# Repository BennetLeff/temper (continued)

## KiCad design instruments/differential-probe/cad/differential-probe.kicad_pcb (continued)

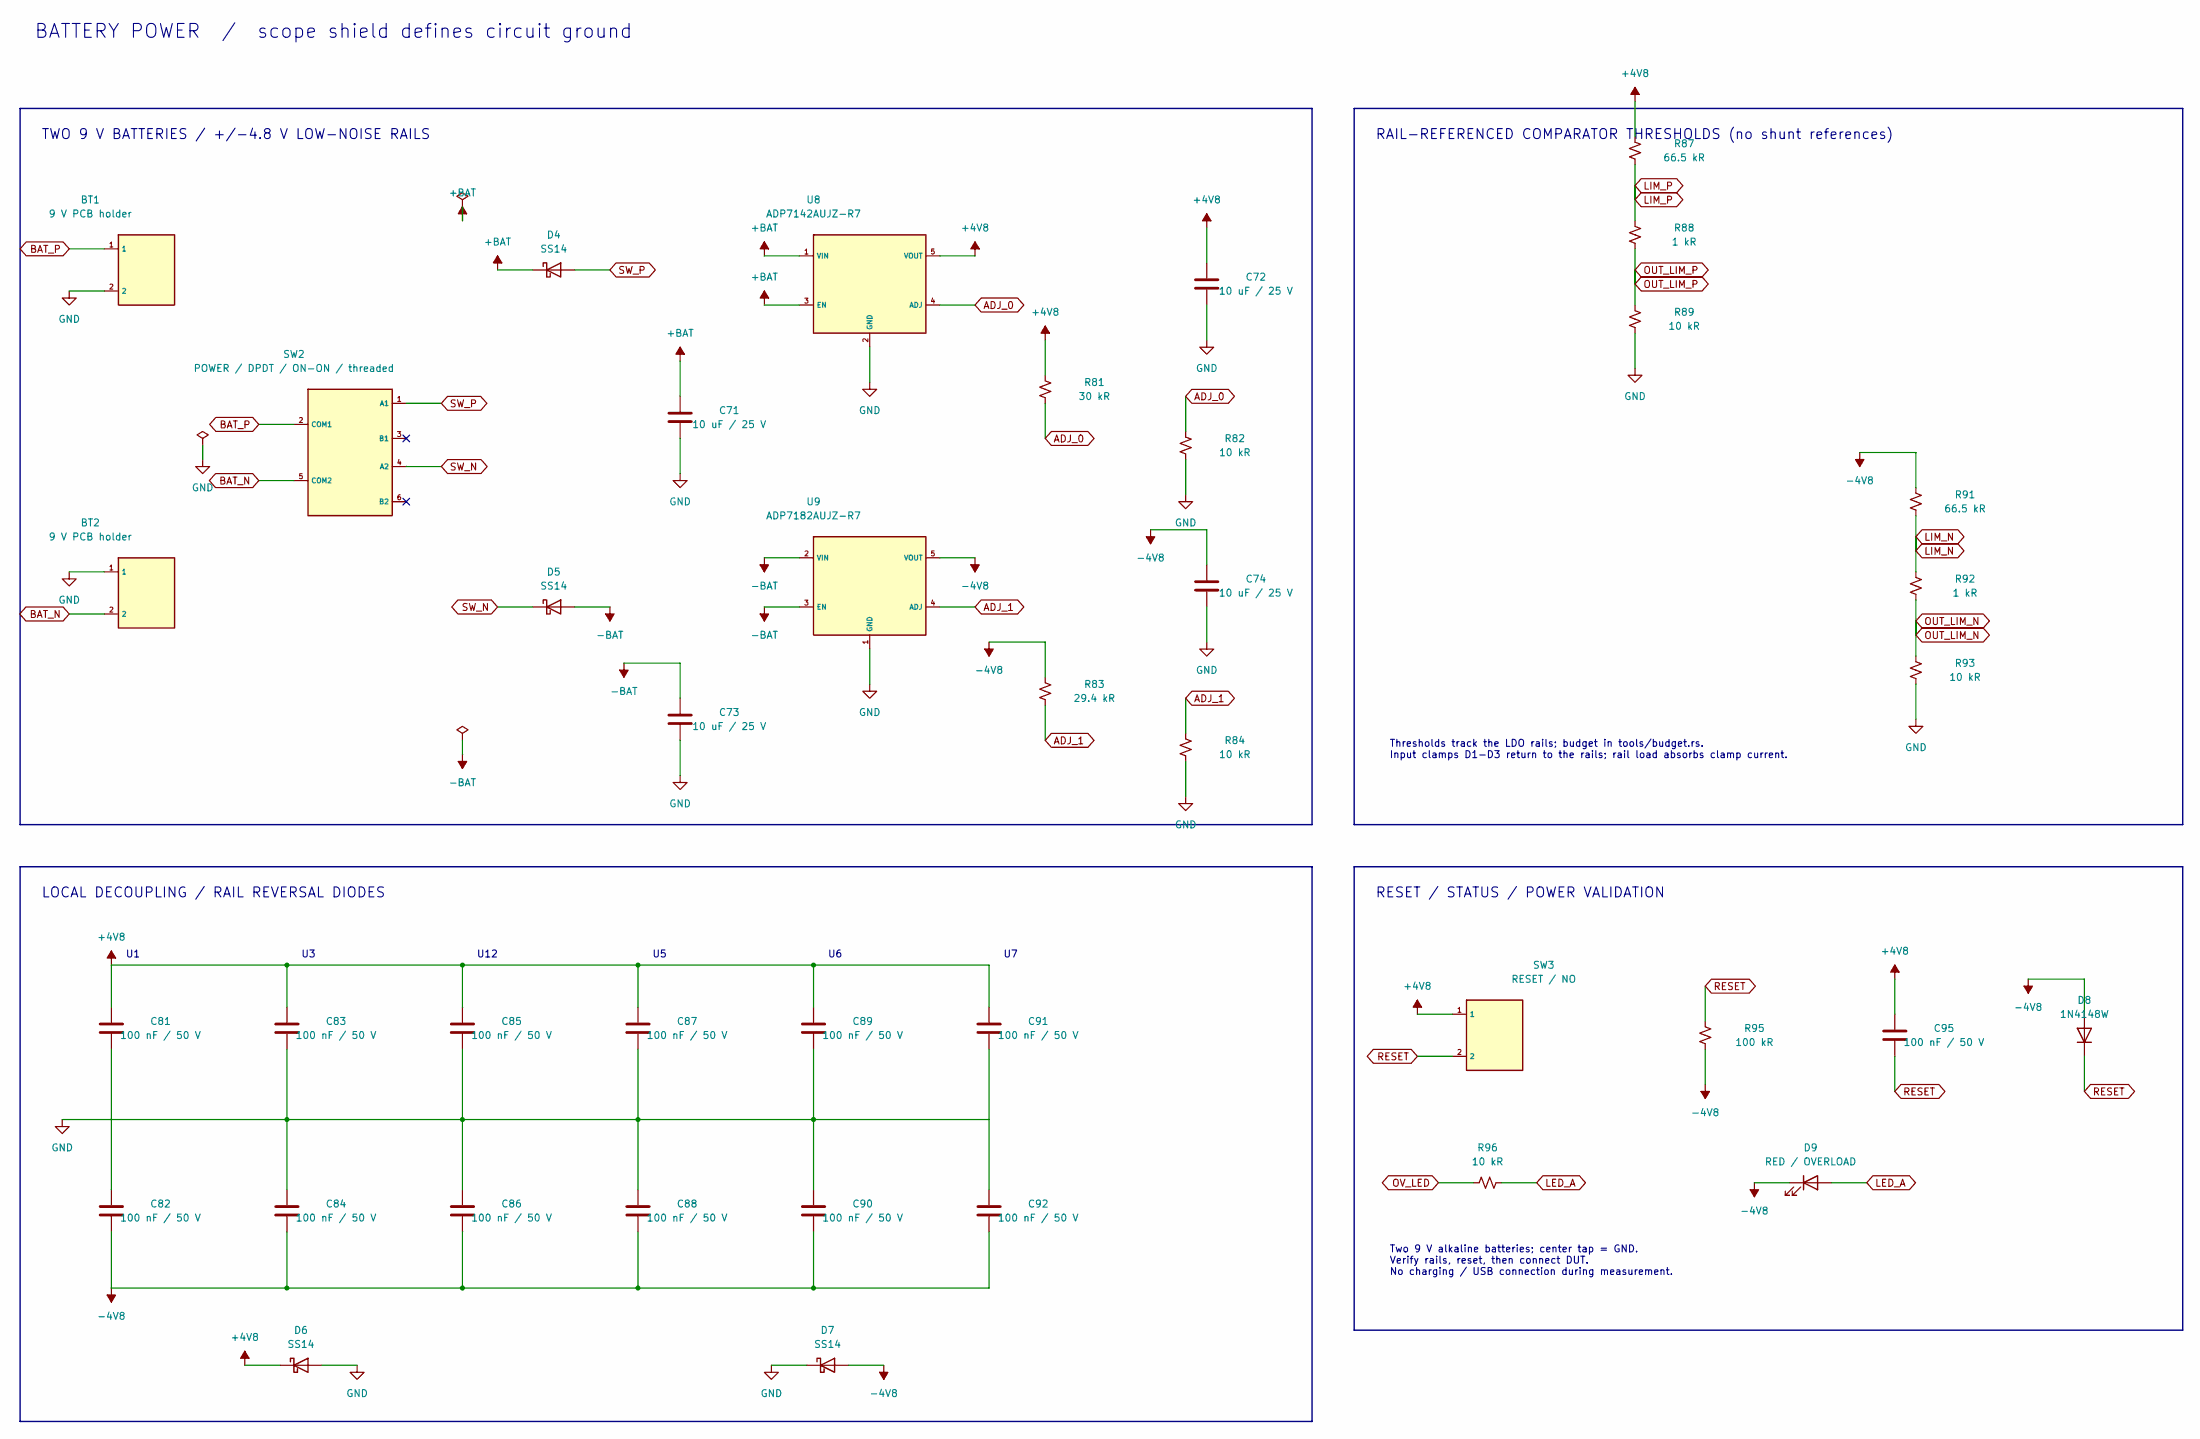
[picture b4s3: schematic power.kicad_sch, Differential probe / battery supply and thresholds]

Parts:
BT1, BT2: 9 V PCB holder; BatteryHolder_MPD_BH9VPC; MPN BH9VPC
C71, C72, C73, C74: 10 uF / 25 V; C_1210_3225Metric; MPN C3225X7R1E106KTJ00N; LCSC C342744
C81, C82, C83, C84, C85, C86, C87, C88, C89, C90, C91, C92, C95: 100 nF / 50 V; C_0805_2012Metric; MPN CC0805KRX7R9BB104; LCSC C49678
D4, D5, D6, D7: SS14; D_SMA; MPN SS14; LCSC C2480
D8: 1N4148W; D_SOD-123; MPN 1N4148W; LCSC C81598
D9: RED / OVERLOAD; LED_0805_2012Metric; MPN NCD0805R1; LCSC C84256
R81: 30 kR; R_0805_2012Metric; MPN RT0805BRD0730KL
R82, R84, R89, R93, R96: 10 kR; R_0805_2012Metric; MPN RT0805BRD0710KL
R83: 29.4 kR; R_0805_2012Metric; MPN RT0805BRD0729K4L
R87, R91: 66.5 kR; R_0805_2012Metric; MPN RT0805BRD0766K5L
R88, R92: 1 kR; R_0805_2012Metric; MPN 0805W8F1001T5E; LCSC C17513
R95: 100 kR; R_0805_2012Metric; MPN 0805W8F1003T5E; LCSC C149504
SW2: POWER / DPDT / ON-ON / threaded; ESwitch_100_M7_DPDT; MPN 100DP1T1B1M7QEH
SW3: RESET / NO; SW_Tactile_CK_PTS645_THT; MPN PTS645SL43-2 LFS; LCSC C221874
U8: ADP7142AUJZ-R7; TSOT-23-5; MPN ADP7142AUJZ-R7; LCSC C514356
U9: ADP7182AUJZ-R7; TSOT-23-5; MPN ADP7182AUJZ-R7; LCSC C514358

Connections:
+4V8: C72.1, C81.1, C83.1, C85.1, C87.1, C89.1, C91.1, C95.1, D6.1 (K), R81.1, R87.1, SW3.1, U8.5 (VOUT); also elsewhere on the board
+BAT: C71.1, D4.1 (K), U8.1 (VIN), U8.3 (EN)
-4V8: C74.1, C82.2, C84.2, C86.2, C88.2, C90.2, C92.2, D7.2 (A), D8.2 (A), D9.1 (K), R83.1, R91.1, R95.2, U9.5 (VOUT); also elsewhere on the board
-BAT: C73.1, D5.2 (A), U9.2 (VIN), U9.3 (EN)
ADJ_0: R81.2, R82.1, U8.4 (ADJ)
ADJ_1: R83.2, R84.1, U9.4 (ADJ)
BAT_N: BT2.2, SW2.5 (COM2)
BAT_P: BT1.1, SW2.2 (COM1)
GND: BT1.2, BT2.1, C71.2, C72.2, C73.2, C74.2, C81.2, C82.1, C83.2, C84.1, C85.2, C86.1, C87.2, C88.1, C89.2, C90.1, C91.2, C92.1, D6.2 (A), D7.1 (K), R82.2, R84.2, R89.2, R93.2, U8.2 (GND), U9.1 (GND); also elsewhere on the board
LED_A: D9.2 (A), R96.2
LIM_N: R91.2, R92.1; also elsewhere on the board
LIM_P: R87.2, R88.1; also elsewhere on the board
OUT_LIM_N: R92.2, R93.1; also elsewhere on the board
OUT_LIM_P: R88.2, R89.1; also elsewhere on the board
OV_LED: R96.1; also elsewhere on the board
RESET: C95.2, D8.1 (K), R95.1, SW3.2; also elsewhere on the board
SW_N: D5.1 (K), SW2.4 (A2)
SW_P: D4.2 (A), SW2.1 (A1)

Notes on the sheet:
BATTERY POWER / scope shield defines circuit ground
TWO 9 V BATTERIES / +/-4.8 V LOW-NOISE RAILS
RAIL-REFERENCED COMPARATOR THRESHOLDS (no shunt references)
Thresholds track the LDO rails; budget in tools/budget.rs. Input clamps D1-D3 return to the rails; rail load absorbs clamp current.
LOCAL DECOUPLING / RAIL REVERSAL DIODES
U12
RESET / STATUS / POWER VALIDATION
Two 9 V alkaline batteries; center tap = GND. Verify rails, reset, then connect DUT. No charging / USB connection during measurement.

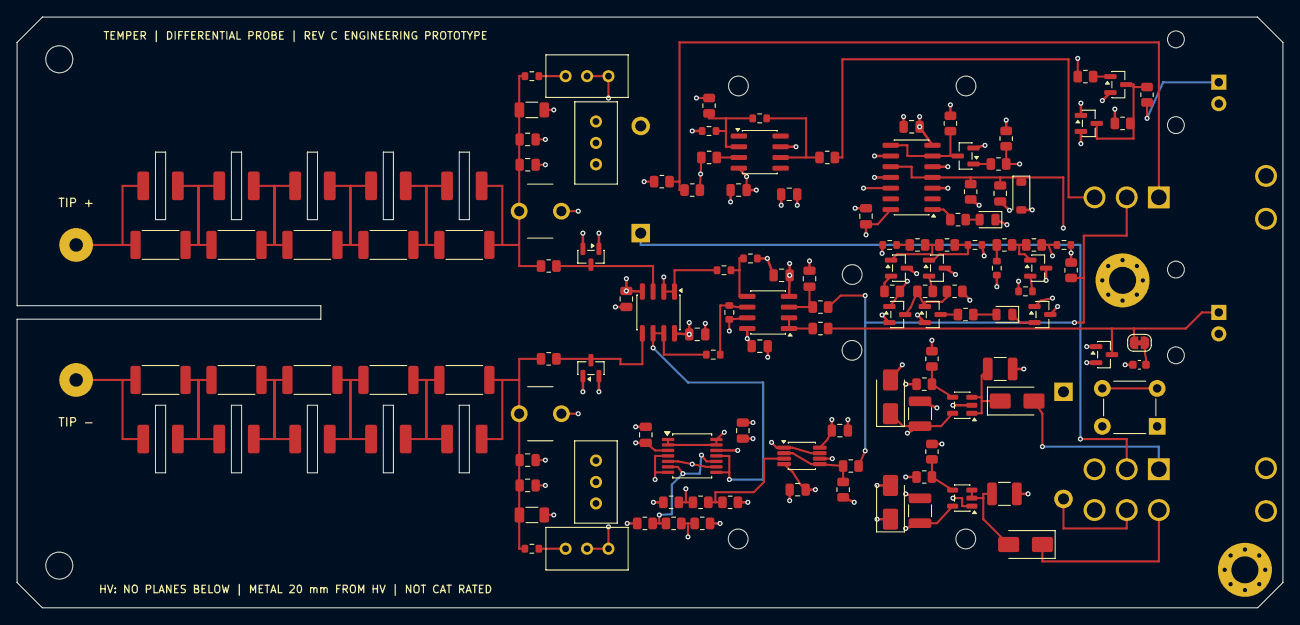
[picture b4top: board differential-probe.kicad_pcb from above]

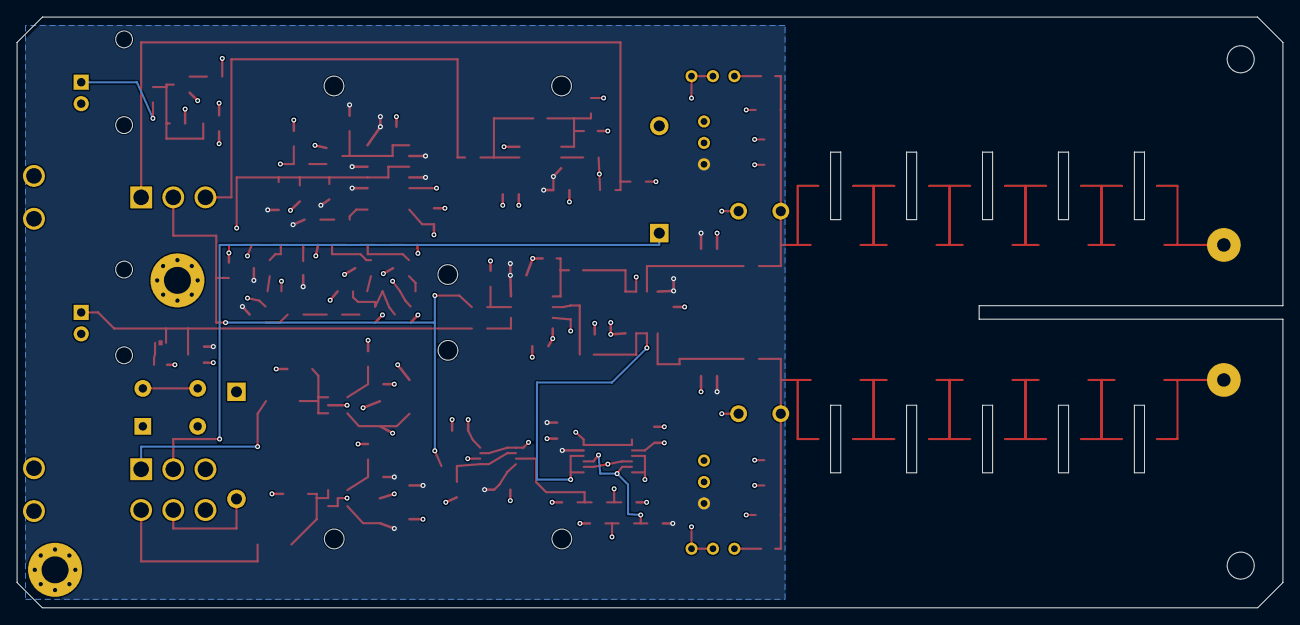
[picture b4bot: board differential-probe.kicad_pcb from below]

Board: 4 copper layers, 150.0 x 70.0 mm, 143 parts (2 on the bottom side), 73 nets.

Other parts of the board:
H1: H1; MountingHole_3.2mm_M3_Pad_Via
H2: H2; MountingHole_3.2mm_M3_Pad_Via
H3: H3; MountingHole_3.2mm_M3
H4: H4; MountingHole_3.2mm_M3
W_HV1: W_HV1; HV_Captive_Lead
W_HV2: W_HV2; HV_Captive_Lead

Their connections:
GND: H1.1, H2.1; also elsewhere on the board
TIP_N: W_HV2.1; also elsewhere on the board
TIP_P: W_HV1.1; also elsewhere on the board

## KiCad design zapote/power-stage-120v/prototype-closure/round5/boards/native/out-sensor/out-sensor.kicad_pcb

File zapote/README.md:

# Zapote

**Board checks:** [ERC, DRC and layout command index](CHECKS.md), or
`make -C zapote help`. Includes native current analysis, before/after comparisons,
Rust owners, test evidence, and the current integration/CI checkpoint.

> **Scope on `main` (landed 2026-10-08).** Five maintained units — RTD, current-sense,
> thermal-sense, interlock, gate-drive — plus `power-stage-120v` and the inverter
> measurement framework (superseded by the 120 V stage's own validation plan; see
> `inverter/U3-MEASUREMENT-READINESS.md`). The Rev38 PFC power entry, the voltage-sense unit, the
> PFC-board bridge/shunt FEM and cooling studies, and their crate modules are
> archived at tags `archive/rev38-power-entry-2026-09-25` and
> `archive/zapote-coil-intake-2026-09-25` (see `docs/archive/REV38.md`). Unit
> evidence runs not read by a check also stay in those tags; a unit
> `ACCEPTANCE.md` path that is absent here resolves there. Bulk solver output
> (`*.gz`, `*.npz`, files over 5 MB) is in release `zapote-evidence-2026-10-08`;
> `python3 zapote/tools/evidence_archive.py fetch` restores it in place.

Zapote is Temper's agent engineering subproject centered on a large Rust
validation suite. The working Python/KiCad editing adapter stays in use.

It shares Temper's product inputs and copies needed existing Rust validators
into focused packages such as `zapote-drc` and `zapote-erc`, retaining tests and
provenance. The agent makes placement and routing decisions; Zapote supplies
explicit board edits, engineering feedback, memory, and recorded execution.
See [ARCHITECTURE.md](ARCHITECTURE.md) for package boundaries and
[VALIDATION.md](VALIDATION.md) for the board-validation objective and coverage
ambition. Replacing the Python adapter is deferred.

The [cooker delivery roadmap](https://github.com/BennetLeff/temper/blob/archive/zapote-coil-intake-2026-09-25/docs/plans/2026-09-10-1627-zapote-cooker-roadmap-plan.md)
sets the order from standalone buck/MCU units through the complete routed board and
physical bring-up. Each milestone adds cooker circuitry, Rust validation coverage
and reusable engineering lessons; implementation detail is added as it approaches.

## Current status

Zapote has a standalone Rust workspace with core, DRC, ERC and harness packages.
The [RTD unit](rtd/unit/ACCEPTANCE.md) exercises the source-to-board flow, and
[model qualification](rtd/model-correctness/README.md) checks the meaning of its
passive-network certificates. Device applicability and brownout timing remain
INDETERMINATE; physical tests are NOT RUN.

The [standalone current-sense / primary OCP unit](current-sense/README.md)
adds a separately compiled Atopile source, routed native PCB, corrected
transformer land pattern, bounded electrical model and Rust source/geometry
checks. Its acceptance record separates digital verification from unrun
physical qualification and procurement gaps.

The [standalone voltage-sense / OVP unit](https://github.com/BennetLeff/temper/blob/archive/zapote-coil-intake-2026-09-25/zapote/voltage-sense/README.md) adds the next separately compiled, routed unit, a corrected ADC divider, source-derived electrical checks and saved-document consistency controls. Its digital construction passes while qualification remains explicit.

The [standalone thermal unit](thermal-sense/README.md) adds two external-NTC channels, loaded-feedback trip/release modeling, exact connectivity controls and a routed native PCB. Rev B adds conditional open-wire detection; physical qualification remains separate.

The [isolated gate-drive unit](gate-drive/README.md) has a routed 100 × 80 mm candidate with clean native ERC/DRC and passing Rust construction checks; physical qualification is unrun. The [active PFC power-entry unit](https://github.com/BennetLeff/temper/blob/archive/zapote-coil-intake-2026-09-25/zapote/power-entry/README.md) preserves the 1,800 W nominal AC-input target. Its 54-component, 230 × 210 mm candidate is routed with zero native ERC/DRC findings or unconnected nets and seven passing Rust construction findings. Qualification remains INDETERMINATE. See the [two-board demo](https://github.com/BennetLeff/temper/blob/archive/zapote-coil-intake-2026-09-25/zapote/demo-gate-power/index.html).

The [Rust coverage inventory](validation/inventory-2026-09-12.json) maps Temper donors to Zapote,
lists the checks recorded for each maintained unit, and orders the next ports.
The `zapote-board` CLI checks physical stackup only. The [check index](CHECKS.md)
lists the separate native layout/current and unit electrical-validation commands.

[Engineering memory](https://github.com/BennetLeff/temper/blob/archive/zapote-coil-intake-2026-09-25/zapote/skills/README.md) connects reviewed, versioned lessons to
construction inputs through Rust selection and a thin process transport (the catalog and
Python transport are archived; the Rust policy remains in `zapote-harness`). The
native KiCad adapters live in `harness-lab/`, the generators in `tools/generators/`
and the atopile base library in `elec-base/src`. The old Python
migration outline is superseded by [MIGRATION.md](https://github.com/BennetLeff/temper/blob/archive/zapote-coil-intake-2026-09-25/zapote/MIGRATION.md).

The [Gmsh + Elmer thermal backend](https://github.com/BennetLeff/temper/blob/archive/zapote-coil-intake-2026-09-25/zapote/thermal/README.md) adds a separate external
electrothermal reference path, orchestrated and checked in Rust. Its copper-bar
benchmark establishes solver setup; it does not qualify the power-entry necks
or replace existing board findings.

## Layout

| Path | Purpose |
|---|---|
| `project.toml` | Zapote identity and shared Temper resource map |
| `AGENTS.md` | Local operating rules for work in this project |
| `Makefile` | Rust build/test and common saved-board gates |
| `CHECKS.md` | Check discovery: commands, scope, code owners, evidence and CI status |
| `layout-quality/` | Native geometry/current feedback and supplied-model check catalog |
| `Cargo.toml`, `packages/` | Rust workspace, validators and harness |
| `ports.toml` | Donor hashes, copied tests and extraction changes |
| `validation/` | Dated donor inventory, per-unit coverage and next-port sequence |
| `thermal/` | Gmsh + Elmer backend scope, native installation and reference evidence |
| `ARCHITECTURE.md` | Rust package ownership and agent/validator contract |
| `experiments/` | Experiment definitions and frozen inputs |
| `skills/` | Versioned agent skills and learned artifacts |
| `artifacts/` | Durable evidence manifests and local artifact indexes |
| `runs/` | Git-ignored runtime output |
| `evidence-archive.json` | Manifest of bulk evidence held in release assets; restore with `tools/evidence_archive.py fetch` |
| `docs/` | Design, migration, and operating notes |

## Commands

```sh
make -C zapote setup
make -C zapote help
make -C zapote check
make -C zapote build
```

`setup` checks Rust workspace metadata, `build` builds its binaries/examples,
and `check` runs release Rust tests, native 120 V layout/current analysis, then
the five-unit acceptance runner. Native commands need the KiCad runtimes listed
in [CHECKS.md](CHECKS.md). `check-boards` runs stackup checks only.

Check any new board with `make -C zapote board-check BOARD=/absolute/path/to/board.kicad_pcb`.
The `zapote-board` Rust CLI reads the actual PCB bytes, hashes them and runs
`DRC.BOARD.STACKUP`; its pass is not a substitute for unit electrical checks
or native ERC/DRC. Register new maintained unit paths in `UNIT_BOARDS` before
acceptance. Historical/frozen artifacts are not modified by these commands.
Legacy buck `qualify-buck` and `engineering` commands remain explicitly delegated.

## Direction

Zapote is not another PCB optimizer. It is the harness layer that makes agent
behavior measurable, repeatable, inspectable, and improvable across Temper's
engineering domains. See `MIGRATION.md` for the planned boundary and the
current source-of-truth decisions.

The [standalone interlock](interlock/README.md) adds seven fault inputs, watchdog/liveness gating and a stateful reset latch. Its source-driven Rust checks evaluate 4,096 gate/state/clock combinations and reject physical connectivity and model mutations. Sensor-liveness production and receiver behavior remain integration obligations.

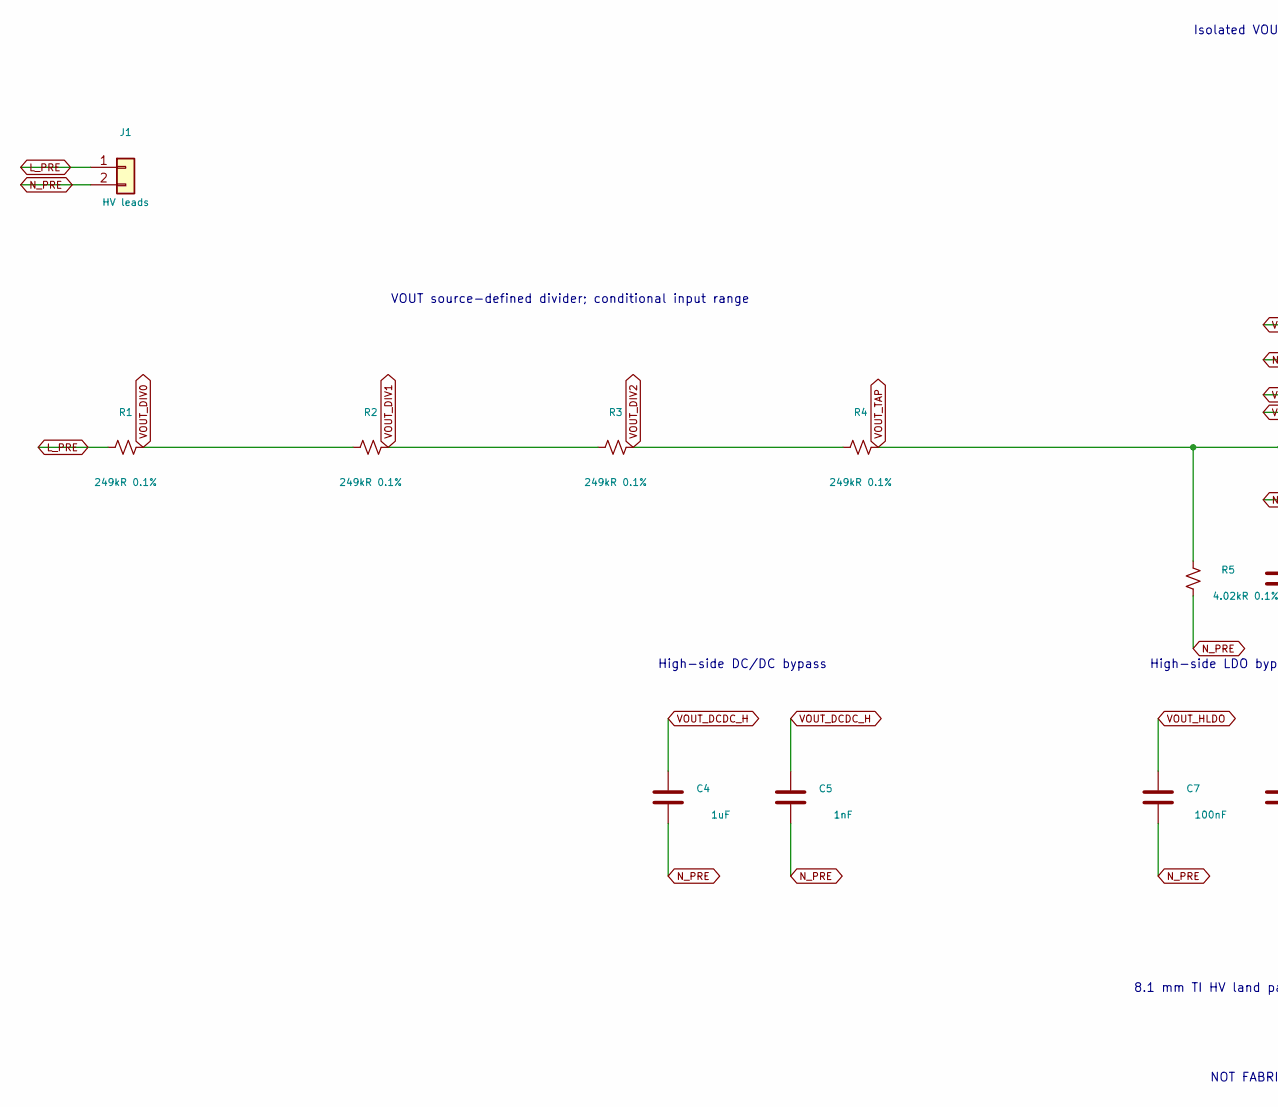
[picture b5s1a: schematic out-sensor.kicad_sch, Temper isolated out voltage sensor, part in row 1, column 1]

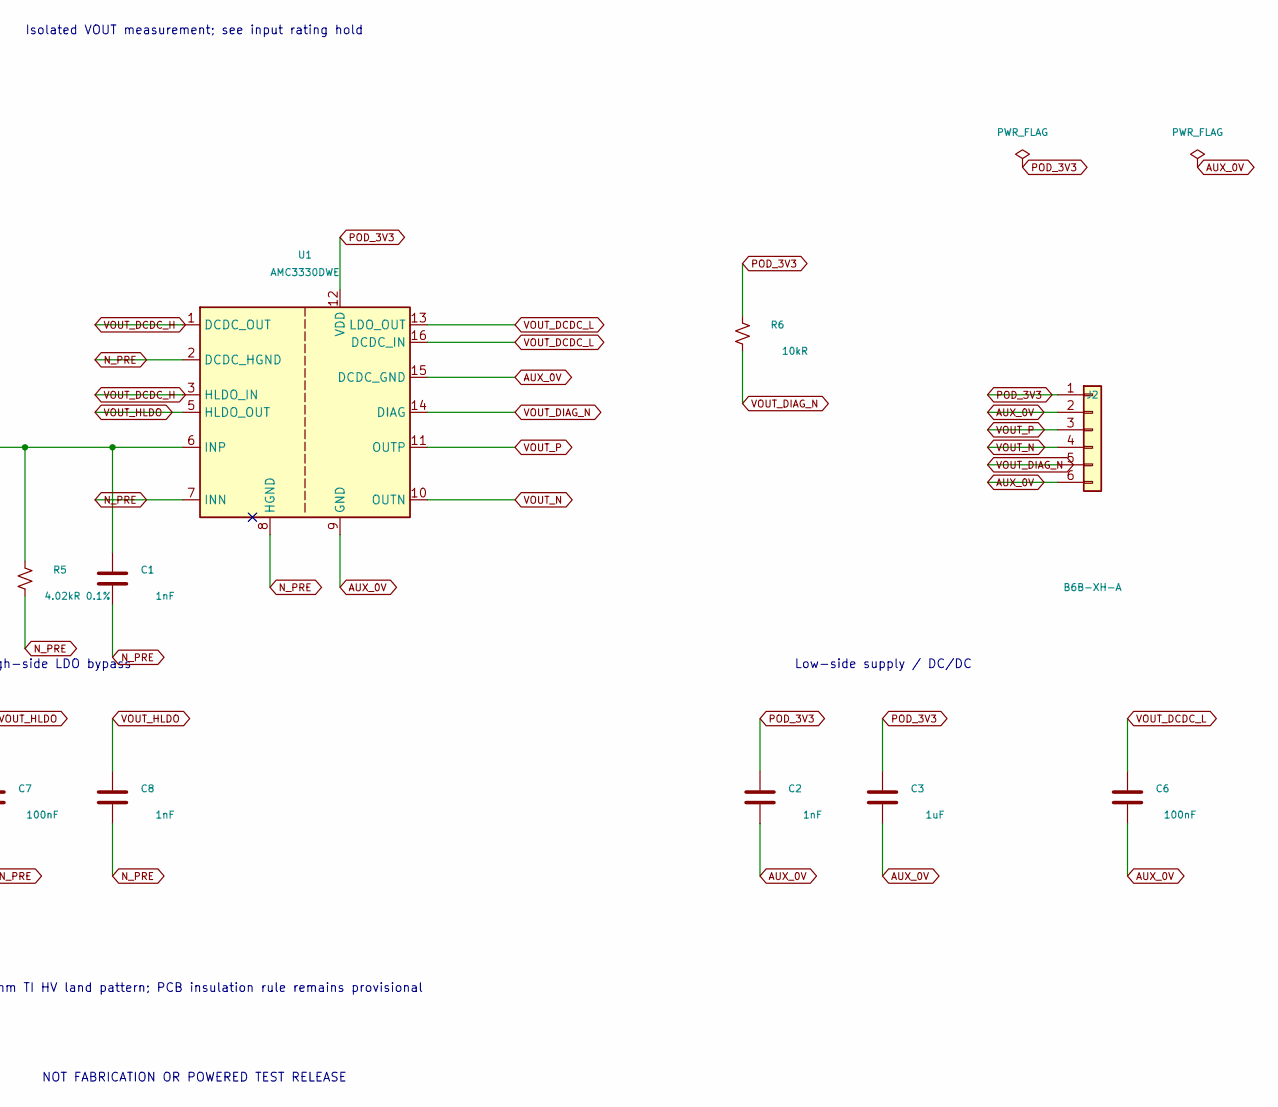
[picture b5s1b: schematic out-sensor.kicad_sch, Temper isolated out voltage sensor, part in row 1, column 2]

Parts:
C1: 1nF; C_0603_1608Metric; MPN 1nF C0603C102J5GACTU
C2: 1nF; C_1206_3216Metric; MPN 1nF 12065C102KAT2A
C3: 1uF; C_1206_3216Metric; MPN 1uF 12063C105KAT2A
C4: 1uF; C_0603_1608Metric; MPN 1uF CGA3E1X7R1E105K080AC
C5, C8: 1nF; C_0603_1608Metric; MPN 1nF C0603C102K5RACTU
C6, C7: 100nF; C_0603_1608Metric; MPN 100nF C0603C104K5RACAUTO
J1: HV leads; HV_WirePair_P25; MPN HV_SOLDER_LEADS_WITH_EXTERNAL_STRAIN_RE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
J2: B6B-XH-A; JST_XH_B6B-XH-A_1x06_P2.50mm_Vertical; MPN B6B-XH-A(LF)(SN)
R1, R2, R3, R4: 249kR 0.1%; R_1206_3216Metric; MPN TNPW1206249KBEEA 249kR 0.1%
R5: 4.02kR 0.1%; R_1206_3216Metric; MPN TNPW12064K02BEEA 4.02kR 0.1%
R6: 10kR; R_0603_1608Metric; MPN 10kR CRCW060310K0FKEA
U1: AMC3330DWE; AMC3330_DWE_HV; MPN AMC3330DWE

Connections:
AUX_0V: C2.2, C3.2, C6.2, J2.2, J2.6, U1.9 (GND), U1.15 (DCDC_GND)
L_PRE: J1.1, R1.1
N_PRE: C1.2, C4.2, C5.2, C7.2, C8.2, J1.2, R5.2, U1.2 (DCDC_HGND), U1.7 (INN), U1.8 (HGND)
POD_3V3: C2.1, C3.1, J2.1, R6.1, U1.12 (VDD)
VOUT_DCDC_H: C4.1, C5.1, U1.1 (DCDC_OUT), U1.3 (HLDO_IN)
VOUT_DCDC_L: C6.1, U1.13 (LDO_OUT), U1.16 (DCDC_IN)
VOUT_DIAG_N: J2.5, R6.2, U1.14 (DIAG)
VOUT_DIV0: R1.2, R2.1
VOUT_DIV1: R2.2, R3.1
VOUT_DIV2: R3.2, R4.1
VOUT_HLDO: C7.1, C8.1, U1.5 (HLDO_OUT)
VOUT_N: J2.4, U1.10 (OUTN)
VOUT_P: J2.3, U1.11 (OUTP)
VOUT_TAP: C1.1, R4.2, R5.1, U1.6 (INP)

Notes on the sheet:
VOUT source-defined divider; conditional input range
Isolated VOUT measurement; see input rating hold
8.1 mm TI HV land pattern; PCB insulation rule remains provisional
High-side DC/DC bypass
High-side LDO bypass
Low-side supply / DC/DC
NOT FABRICATION OR POWERED TEST RELEASE

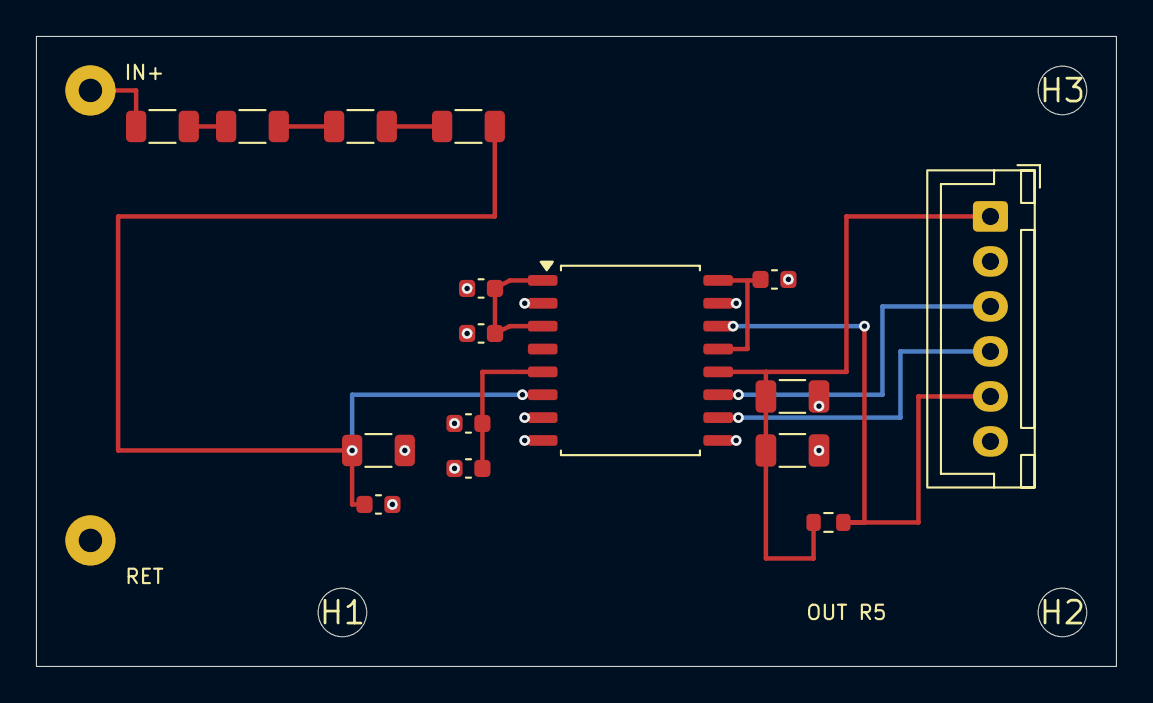
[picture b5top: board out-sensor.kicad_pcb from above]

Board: 2 copper layers, 60.0 x 35.0 mm, 20 parts (0 on the bottom side), 14 nets.

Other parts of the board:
H1, H2, H3: (no value)

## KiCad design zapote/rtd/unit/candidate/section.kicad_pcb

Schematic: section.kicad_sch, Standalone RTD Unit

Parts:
C1, C2, C4, C5, C6, C7, C8, C9: C0603C104K5RACTU; C_0603_1608Metric
C3: C0603C102J5GACTU; C_0603_1608Metric
J1: B4B-XH-A(LF)(SN); JST_XH_B4B-XH-A_1x04_P2.50mm_Vertical
J2: FTSH-105-01-F-D; FTSH-105-01-F-D_2x5_P1.27mm
R1: RG2012V-431-W-T1; R_0805_2012Metric
R2, R3: RC0603JR-071ML; R_0603_1608Metric
R4, R5, R6, R7: RC0603FR-0733RL; R_0603_1608Metric
R8: BLM18AG121SN1D; L_0603_1608Metric
R9: ERA-3AEB6192V; R_0603_1608Metric
R10, R12, R16: ERA-3AEB103V; R_0603_1608Metric
R11: ERA-3AEB5901V; R_0603_1608Metric
R13, R14: RC0603FR-07100KL; R_0603_1608Metric
R15: ERA-3AEB1652V; R_0603_1608Metric
R17, R18: RC0603FR-0710KL; R_0603_1608Metric
U1: MAX31865AAP+; SSOP-20_3.9x8.7mm_P0.635mm
U2: REF2025AIDDCR; SOT-23-5
U3, U4: TLV3201AIDBVR; SOT-23-5
U5: SN74LVC1G08DBVR; SOT-23-5
U6: TPS389001DSER; TPS389001DSER_WSON-6_DSE
U7: SN74LVC1G38DBVR; SOT-23-5

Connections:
+3V3: C2.1, C4.1, C8.1, C9.1, J2.1, R8.1, R17.1, R18.1, U1.2, U2.3, U2.4, U6.3, U6.4, U7.5
RTD_AVDD: C1.1, C5.1, C6.1, C7.1, R8.2, R15.1, U1.3, U3.5, U4.5, U5.5
RTD_CS_N: J2.7, R6.1
RTD_DRDY: J2.8, U1.1
RTD_HW_FAULT: J2.9, R18.2, U7.4
RTD_SCK: J2.4, R4.1
RTD_SDI: J2.5, R5.1
RTD_SDO: J2.6, R7.2
SHARED_REF_2V5: J2.10, U2.5
bias: R1.1, R2.2, R3.2, U1.4, U1.5
cs_n: R6.2, U1.16
ct: U6.5
gnd: C1.2, C2.2, C4.2, C5.2, C6.2, C7.2, C8.2, C9.2, J2.2, J2.3, R12.2, R14.2, R16.2, U1.9, U1.13, U1.18, U1.19, U2.2, U3.2, U4.2, U5.3, U6.2, U7.3
inn: R9.2, R10.1, U3.4
inp: R11.2, R12.1, U4.3
nc3: U1.20
refin_n: R1.2, U1.6, U1.7
reset: R17.2, U6.6, U7.2
rtd_force_n: J1.4, U1.12
rtd_force_p: J1.1, U1.8
rtd_pan.high_window-out: U4.1, U5.2
rtd_pan.low_window-out: U3.1, U5.1
rtd_sense_n: C3.2, J1.3, R3.1, R10.2, U1.11
rtd_sense_p: C3.1, J1.2, R2.1, R13.1, U1.10
sclk: R4.2, U1.15
sdi: R5.2, U1.14
sdo: R7.1, U1.17
sense: R15.2, R16.1, U6.1
vbias: R9.1, R11.1, U2.1
window_rtdin_p: R13.2, U3.3, U4.4
y: R14.1, U5.4, U7.1

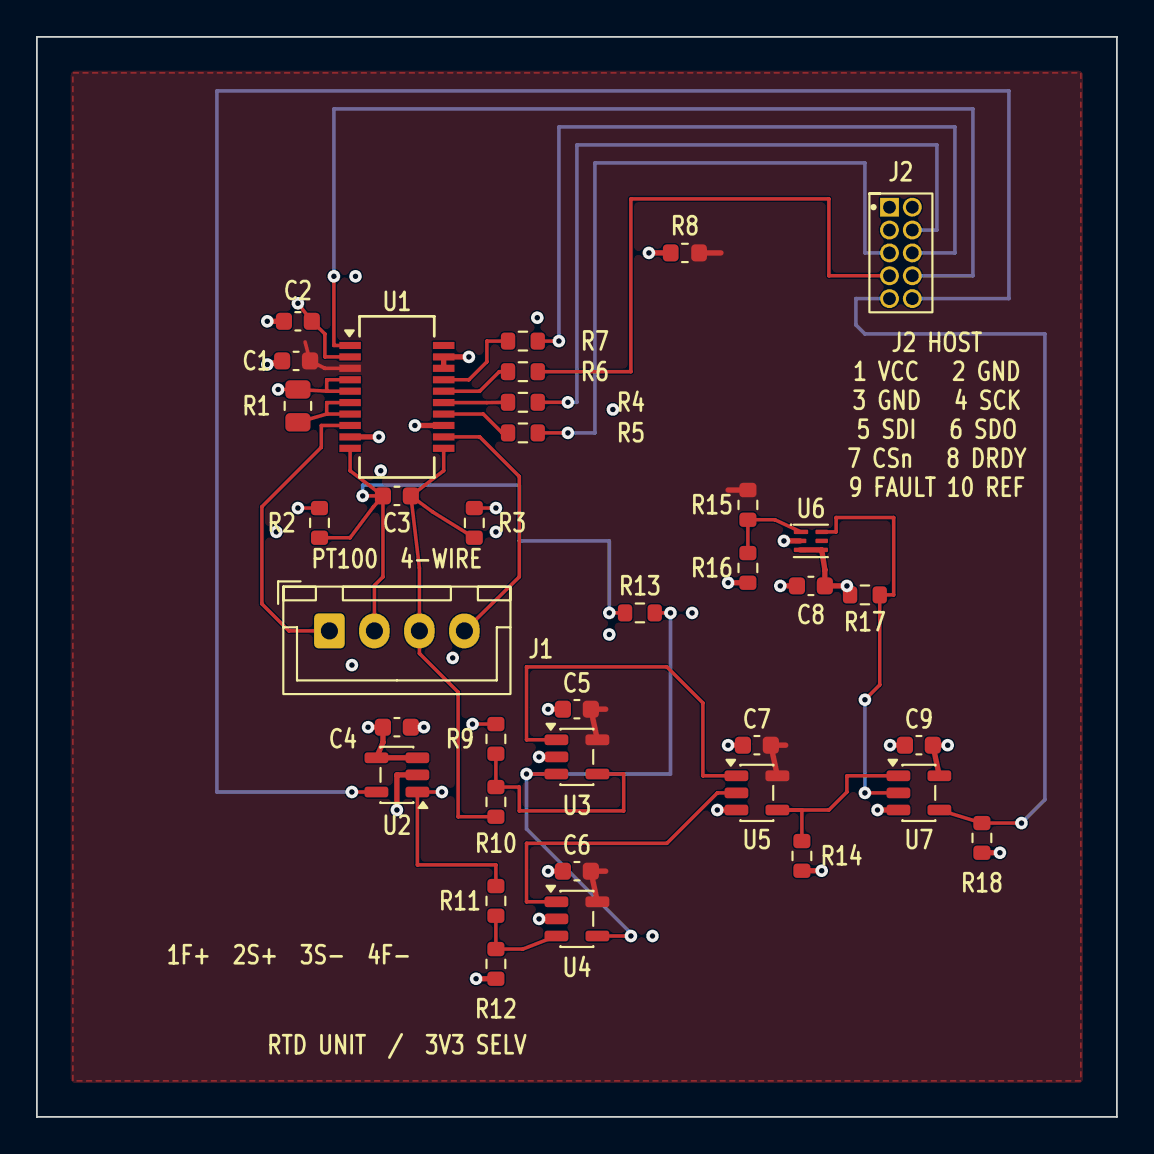
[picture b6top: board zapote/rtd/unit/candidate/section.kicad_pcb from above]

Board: 4 copper layers, 60.0 x 60.0 mm, 36 parts (0 on the bottom side), 29 nets.

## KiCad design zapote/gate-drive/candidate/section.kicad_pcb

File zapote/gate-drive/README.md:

# Standalone isolated dual gate drive

This unit is source-owned by `elec/src/gate_drive_unit.ato` and is compiled
through Atopile 0.2.69. The selected driver is TI UCC21550BDWKR, the
orderable tape-and-reel suffix for the verified DWK 14-pin package. Its
physical pins are 1–11 and 14–16; pins 12 and 13 are absent.

The control boundary is J1 (PWM_H, PWM_L, PERMIT, CTRL_GND). J2 is the one
externally provided isolated 15 V low-side supply and HV_RETURN boundary.
The high-side supply is a bootstrap from that floating rail through D1 and
C4, referenced to the high-side Kelvin return. J3 and J4 expose gate/Kelvin-
return pairs; HV_RETURN is carried by J2 and J4. Q1 (AO3400A, exact
1=G/2=S/3=D map) is the source-level PERMIT inverter, with a 100 kΩ gate
pulldown and 10 kΩ DIS pullup.
No control return is tied to HV_RETURN, and no local transformer or DC/DC is
claimed.

`source-build-09/` is the current successful source compile/export. The final
routed board is `candidate/section.kicad_pcb`, with route08, native extraction,
Rust construction checks, and native ERC/DRC receipts retained under
`evidence/`. The Edge.Cuts centreline is exactly 100 mm by 80 mm; its 0.10 mm
stroke makes the measured outer bounding box 100.10 mm by 80.10 mm. D1 is the
exact Vishay UF4007-E3/54 DO-41 through-hole
part. U1 uses a labeled, low-fidelity 14-lead DWK visualization; its physical
pins are 1–11 and 14–16. This is not a mechanical qualification model.

The validated construction contract uses one externally provided isolated
15 V low-side supply at J2 and a bootstrap high-side supply. The 39 kOhm DT
resistor is a conditional interpolation envelope, not a published TI timing
guarantee. Bootstrap startup, loaded switching, thermal behavior, and timing
measurement remain unrun.

Selected memory notes used: `rtd-mem-001`, `current-sense-mem-001`,
`voltage-sense-mem-001`, `thermal-sense-mem-001`, `thermal-sense-mem-002`,
and `interlock-mem-001`. Their procedural effect was to keep model claims
separate from physical qualification, verify exact package geometry and pin
names, preserve domain-specific returns, and read nested native ERC findings.

Source SHA-256 and compiled artifact hashes are recorded in
`source-build-09/build-receipt.json` and `evidence/native-09.json`.

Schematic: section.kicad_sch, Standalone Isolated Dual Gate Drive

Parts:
C1, C2: C0603C104K5RACTU; C_0603_1608Metric
C3, C4: GRM32ER71H106KA12L; C_1210_3225Metric
D1: UF4007-E3/54; D_DO-41_SOD81_P10.16mm_Horizontal
J1: B4B-XH-A(LF)(SN); JST_XH_B4B-XH-A_1x04_P2.50mm_Vertical
J2, J3, J4, J5: 61300211121; PinHeader_1x02_P2.54mm_Vertical
Q1: AO3400A; SOT-23
R1: RC0603FR-071KL; R_0603_1608Metric
R2: RC0603FR-07100KL; R_0603_1608Metric
R3: RC0603FR-0710KL; R_0603_1608Metric
R4: RC0603FR-0739KL; R_0603_1608Metric
R5, R7: RC1206FR-073R9L; R_1206_3216Metric
R6, R8: RC0603FR-072K2L; R_0603_1608Metric
U1: UCC21550BDWKR; SOIC16W_Isolated

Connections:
ctrl_gnd: C1.2, J1.4, J5.2, Q1.2 (S), R2.2, R4.2, U1.4 (GNDI)
dis: Q1.3 (D), R3.1, U1.5 (DIS)
dt: R4.1, U1.6 (DT)
g: Q1.1 (G), R1.2, R2.1
gate_h_kelvin: C4.2, J3.2, R6.2, U1.14 (VSSA)
gate_h_out: J3.1, R5.2, R6.1
gate_l_kelvin: C2.2, C3.2, J2.2, J4.2, R8.2, U1.9 (VSSB)
gate_l_out: J4.1, R7.2, R8.1
nc_7: U1.7 (NC_7)
outa: R5.1, U1.15 (OUTA)
outb: R7.1, U1.10 (OUTB)
permit: J1.3, R1.1
pwm_h: J1.1, U1.1 (INA)
pwm_l: J1.2, U1.2 (INB)
v3v3: C1.1, J5.1, R3.2, U1.3 (VCCI_1), U1.8 (VCCI_2)
v15_ls: C2.1, C3.1, D1.2, J2.1, U1.11 (VDDB)
vdda: C4.1, D1.1, U1.16 (VDDA)

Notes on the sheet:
CONTROL / J1: PWM_H, PWM_L, PERMIT, CTRL_GND
ISOLATED LS SUPPLY / J2: +15V_LS, HV_RETURN
GATE OUTPUTS / J3,J4: GATE + KELVIN RETURN
Q1 AO3400A: PERMIT high pulls DIS low; floating PERMIT is disabled

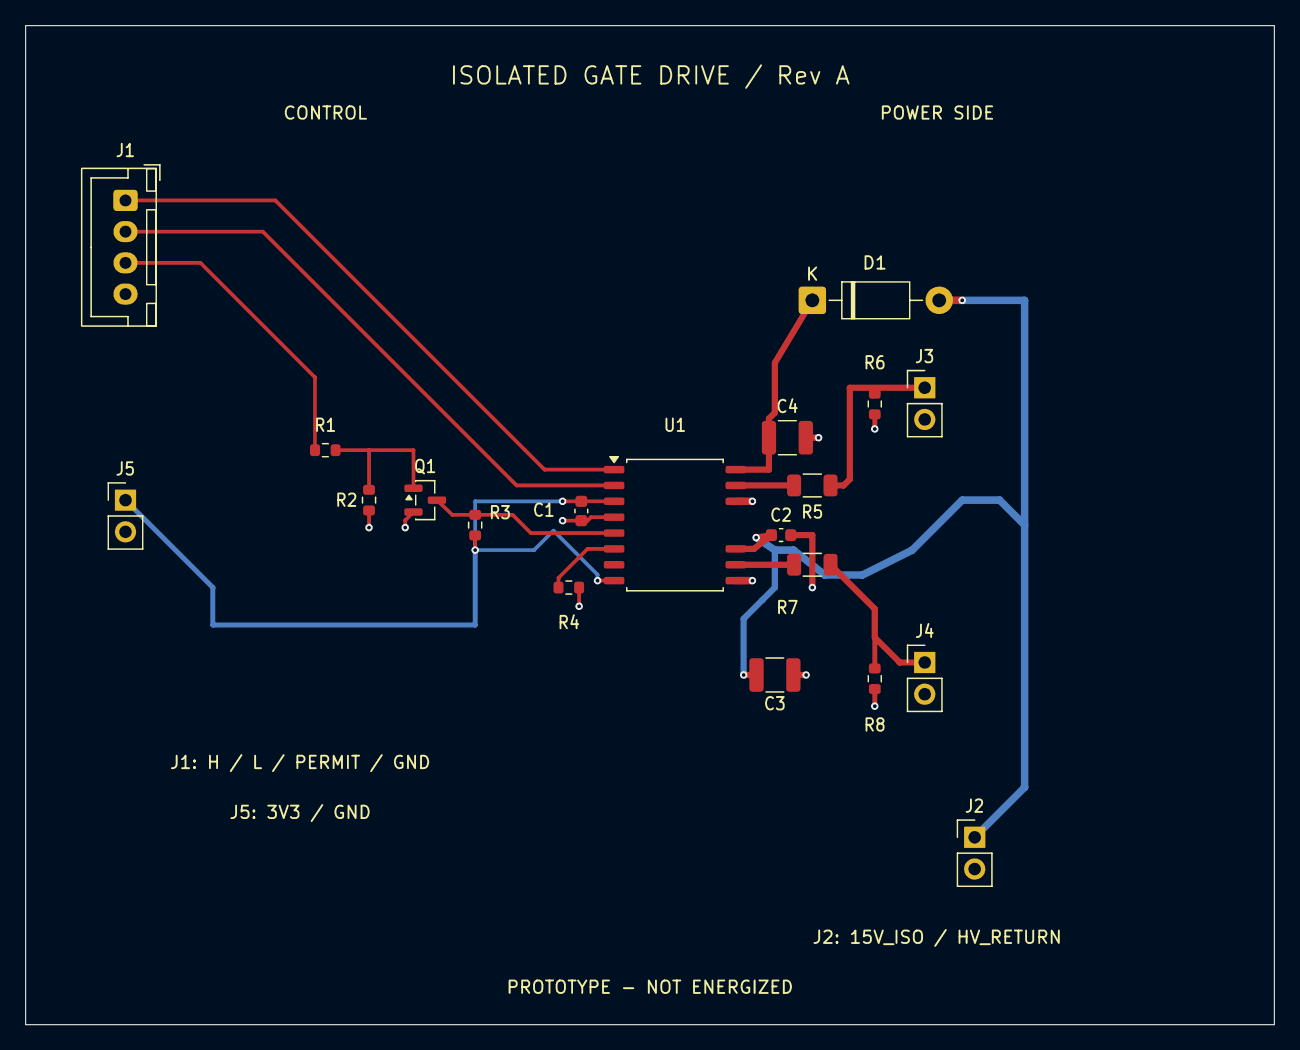
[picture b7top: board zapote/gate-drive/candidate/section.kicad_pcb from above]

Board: 2 copper layers, 100.0 x 80.0 mm, 20 parts (0 on the bottom side), 16 nets.

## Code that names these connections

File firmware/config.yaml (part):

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    units: "pulses/rev"
    doc: >-
      J10 blower FG pulses per revolution (DECISIONS C28: Delta BFB1012VH-F00,
      FG open collector into GPIO3 / PCNT). UNVERIFIED: the Delta sample spec
      does not state it; 2 is the common DC-blower value. Measure on the bench
      (FG frequency vs a strobe / optical rpm at a fixed V_BLOWER) and set it
      here; the stall threshold (thermal_mgmt.h BLOWER_STALL_RPM) is in rpm.
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
  # BIAS_GOOD read-back (power board J4.1, OPEN-ITEMS B13 H2) under option P (power-stage
  # validation-results/11-candidates/c50-permit-gate): U46.A is driven from PERMIT through R135
  # 100 k, so BIAS_GOOD = bias_ok AND PERMIT. Timing at J4.1 / GPIO35 (c50 section 2, class C):
  # >= VIH <= 0.53 ms after PERMIT rises, <= VIL <= 0.36 ms after it falls. The checks:
  # platform_bias_* (components/platform/platform_logic.c) and the binding's start sequence
  # (components/power/n21_binding.c).
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    units: "ms"
    doc: >-
      Check 1 (low with PERMIT low): a control-loop sample is judged only once
      the PERMIT read-back (PERMIT_RB, GPIO36) has been low for at least this
      long; BIAS_GOOD must then read low. 2 ms is 5.6 x the 0.36 ms worst-case
      fall of GPIO35 after PERMIT falls (c50 README section 2: hold-node bleed
      <= 90 us plus the J4.1 220 k / 10 k / 1 MOhm / 1 nF RC to VIL), so a
      healthy board never fails it. The low time is counted from the
      binding's last RUN_EN change when that falls between two samples
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      long afterwards before the pads are released (controller DECISIONS
      C39); otherwise RUN_EN drops again and the start is refused with "NO
      POWER BIAS" (not a fault). 2 ms is 3.8 x the 0.53 ms worst-case rise of
      GPIO35 after PERMIT (pump restart <= 11.8 us, R135 100 k x 15 pF
      <= 1.8 us, then the J4.1 RC, tau 177-198 us, to VIH), and it also covers
      the drivers' enable (<= 13.6 us plus the unpublished 2EDR8259X
      DIS-to-output delay) before the first turn-off command reaches the
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
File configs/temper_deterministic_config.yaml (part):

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  grid_alignment: true

# Component spacing constraints
# The 'tier' field determines if a constraint is hard (filter rejects) or soft (scorer penalizes)
minimum_spacing:
  # Hard constraint: High-power MOSFETs must be separated for thermal management
  - components: ["Q1", "Q2"]
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        max_distance_mm: 20.0
        tier: "soft"

# EXP-11: Signal-to-HV clearance constraints for gate drive routing
# These ensure gate driver outputs are placed close enough to MOSFET gates
# that signal routes don't need to pass near HV pins (6mm IEC 60335 creepage)
signal_hv_clearances:
  - name: "gate_h_clearance"
    signal_component: "U_GATE"
    signal_pin: "15"          # OUTA (high-side gate output)
    target_component: "Q1"
    target_pin: "1"           # Gate pin
    hv_component: "Q1"
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
  - name: "gate_l_clearance"
    signal_component: "U_GATE"
    signal_pin: "10"          # OUTB (low-side gate output)
    target_component: "Q2"
    target_pin: "1"           # Gate pin
    hv_component: "Q2"
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placement_proximity:
  - name: "ugate_to_rgateh"
    from_component: "U_GATE"
    from_pin: "15"            # OUTA
    to_component: "R_GATE_H"
    to_pin: "1"
    max_distance_mm: 12.0
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
  - name: "ugate_to_rgatel"
    from_component: "U_GATE"
    from_pin: "10"            # OUTB
    to_component: "R_GATE_L"
    to_pin: "1"
    max_distance_mm: 12.0
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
